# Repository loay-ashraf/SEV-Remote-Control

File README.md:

# SEV Remote Control
Smart Electric Vehicle remote control implemented using AVR 8-bit microcontroller and Android companion app as a part of EV car conversion graduation project for Mechatronics Engineering Bachelor - Fall 2018.

## Overview
This section gives an overview of the system.

### Concept

SEV remote control is done via means of bluetooth communication between AVR controller board and any bluetooth-enabled device (Android smartphone for example).

### System Layout
System is divided into two separate modules that communicate with each other to acheive the desired output, which are:

#### SEV Controller Board Module

Controller board controls a set of relays and DAC units each connected to a specific actuator in the car.

#### SEV Companion App Module

Companion app sends commands via bluetooth to control each actuator.

## Discussion
This section discusses desicions made regarding design and implementation.

### Microcontroller

We opted for ATmega32 for SEV controller board as it has USART module and enough pins to control relays and DACs.

### Communication Protocol

We used USART protocol in order to communicate with the HC-05 bluetooth module.

### Android IDE

We used free MIT App Inventor as we lacked experience in Android app development while App Inventor offered shallow learning curve and a ton of tutorials available.

## Screenshots

[Screenshots of the companion app](Software/Companion%20App/Screenshots)

## Built With
- Atmel Studio 7 - The official AVR IDE
- AVR-gcc V5.4 - C compiler
- GNU Make - auto-generated makefile
- MIT App Inventor - Android IDE
- CadSoft EAGLE - PCB design tool

## Authors
Loay Ashraf - <loay.ashraf.96@gmail.com>

Mohamed Gamal - <muhammed.gamal051@gmail.com>

## License
This project is licensed under the MIT License - see the LICENSE.md file for details

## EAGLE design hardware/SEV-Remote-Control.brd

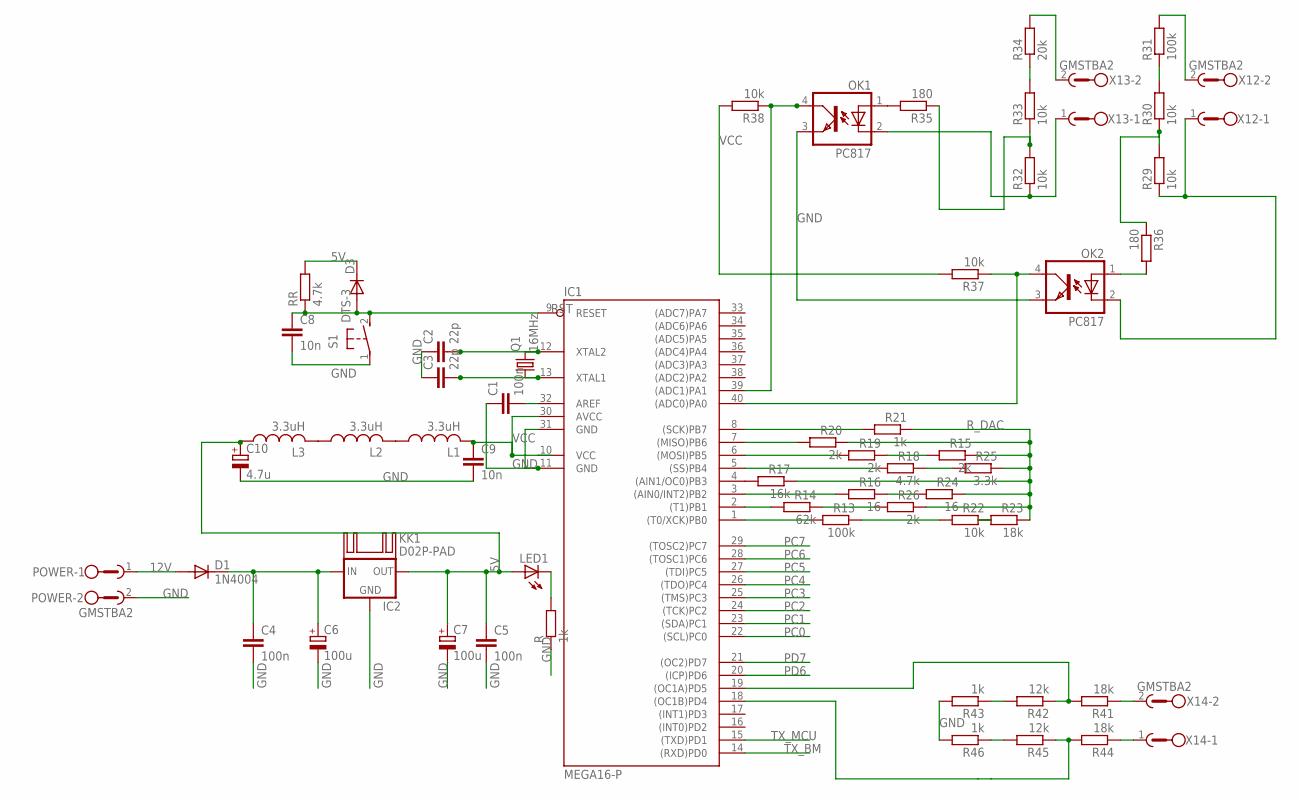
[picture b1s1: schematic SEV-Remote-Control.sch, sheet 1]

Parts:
C1, C4, C5: 100n; C025-025X050
C2, C3: 22p; C025-025X050
C6, C7: 100u; E2,5-6
C8, C9: 10n; C025-025X050
C10: 4.7u; E2,5-6
D1: 1N4004; DO41-10
D3: 1N4148DO35-10; DO35-10
IC1: MEGA16-P; DIL40
IC2: 78XXS
KK1: D02P-PAD; D02PA-PAD
L1, L2, L3: 3.3uH; 0207/7
LED1: LED5MM
OK1, OK2: PC817; DIL04
POWER: GMSTBA2
Q1: 16MHz; HC49/S
R, R21, R43, R46: 1k; 0207/10
R13, R31: 100k; 0207/10
R14: 62k; 0207/10
R15, R19, R20, R26: 2k; 0207/10
R16, R24: 16; 0207/10
R17: 16k; 0207/10
R18: 4.7k; 0207/10
R22, R29, R30, R32, R33, R37, R38: 10k; 0207/10
R23, R41, R44: 18k; 0207/10
R25: 3.3k; 0207/10
R34: 20k; 0207/10
R35, R36: 180; 0207/10
R42, R45: 12k; 0207/10
RR: 4.7k; 0207/10
S1: DTS-3
X12, X13, X14: GMSTBA2

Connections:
5V: C5.1, C7.+, C10.+, D3.C, IC2.OUT, L3.1, LED1.A, RR.2
12V: D1.A, POWER.1; also elsewhere on the board
GND: C1.1, C2.1, C3.1, C4.2, C5.2, C6.-, C7.-, C8.2, C9.2, C10.-, IC1.11 (GND), IC1.31 (GND), IC2.GND, OK1.3 (EMIT), OK2.3 (EMIT), POWER.2, R.1, R43.2, R46.2, S1.1; also elsewhere on the board
IN: C4.1, C6.+, D1.C, IC2.IN
unnamed: R15.2, R19.1
unnamed: R13.1, R22.2
unnamed: LED1.K (C), R.2
unnamed: C2.2, IC1.12 (XTAL2), Q1.2
unnamed: R22.1, R23.2
unnamed: C1.2, IC1.32 (AREF)
unnamed: R16.1, R24.2
unnamed: C3.2, IC1.13 (XTAL1), Q1.1
unnamed: R18.1, R25.2
unnamed: R14.1, R26.2
unnamed: L1.1, L2.2
unnamed: L2.1, L3.2
unnamed: R29.2, R30.1, R36.1
unnamed: R30.2, R31.1
unnamed: R31.2, X12.2
unnamed: IC1.40 ((ADC0)PA0), OK2.4 (COL), R37.1
unnamed: OK1.1 (A), R35.2
unnamed: R33.2, R34.1
unnamed: R34.2, X13.2
unnamed: OK1.2 (C), R32.1, X13.1
unnamed: R32.2, R33.1, R35.1
unnamed: OK2.1 (A), R36.2
unnamed: IC1.2 ((T1)PB1), R14.2
unnamed: OK2.2 (C), R29.1, X12.1
unnamed: IC1.39 ((ADC1)PA1), OK1.4 (COL), R38.1
unnamed: R44.1, X14.1
unnamed: IC1.1 ((T0/XCK)PB0), R13.2
unnamed: IC1.3 ((AIN0/INT2)PB2), R16.2
unnamed: IC1.4 ((AIN1/OC0)PB3), R17.2
unnamed: IC1.5 ((SS)PB4), R18.2
unnamed: IC1.6 ((MOSI)PB5), R19.2
unnamed: IC1.7 ((MISO)PB6), R20.2
unnamed: IC1.8 ((SCK)PB7), R21.2
unnamed: R41.1, X14.2
unnamed: IC1.19 ((OC1A)PD5), R41.2, R42.1
unnamed: IC1.18 ((OC1B)PD4), R44.2, R45.1
unnamed: R42.2, R43.1
unnamed: R45.2, R46.1
PC0: IC1.22 ((SCL)PC0); also elsewhere on the board
PC1: IC1.23 ((SDA)PC1); also elsewhere on the board
PC2: IC1.24 ((TCK)PC2); also elsewhere on the board
PC3: IC1.25 ((TMS)PC3); also elsewhere on the board
PC4: IC1.26 ((TDO)PC4); also elsewhere on the board
PC5: IC1.27 ((TDI)PC5); also elsewhere on the board
PC6: IC1.28 ((TOSC1)PC6); also elsewhere on the board
PC7: IC1.29 ((TOSC2)PC7); also elsewhere on the board
PD6: IC1.20 ((ICP)PD6); also elsewhere on the board
PD7: IC1.21 ((OC2)PD7); also elsewhere on the board
RST: C8.1, D3.A, IC1.9 (RESET), RR.1, S1.2
R_DAC: R15.1, R17.1, R20.1, R21.1, R23.1, R24.1, R25.1, R26.1; also elsewhere on the board
TX_BM: IC1.14 ((RXD)PD0); also elsewhere on the board
TX_MCU: IC1.15 ((TXD)PD1); also elsewhere on the board
VCC: C9.1, IC1.10 (VCC), IC1.30 (AVCC), L1.2, R37.2, R38.2; also elsewhere on the board

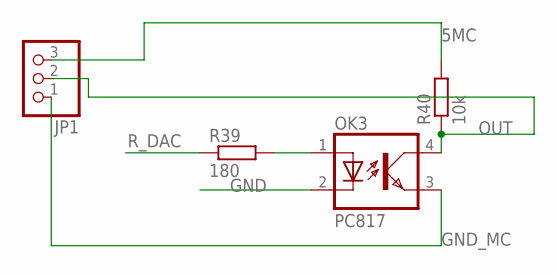
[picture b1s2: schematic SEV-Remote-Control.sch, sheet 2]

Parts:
JP1: PINHD-1X3; 1X03
OK3: PC817; DIL04
R39: 180; 0207/10
R40: 10k; 0207/10

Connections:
5MC: JP1.3, R40.2
GND: OK3.2 (C); also elsewhere on the board
GND_MC: JP1.1, OK3.3 (EMIT)
unnamed: OK3.1 (A), R39.2
OUT: JP1.2, OK3.4 (COL), R40.1
R_DAC: R39.1; also elsewhere on the board

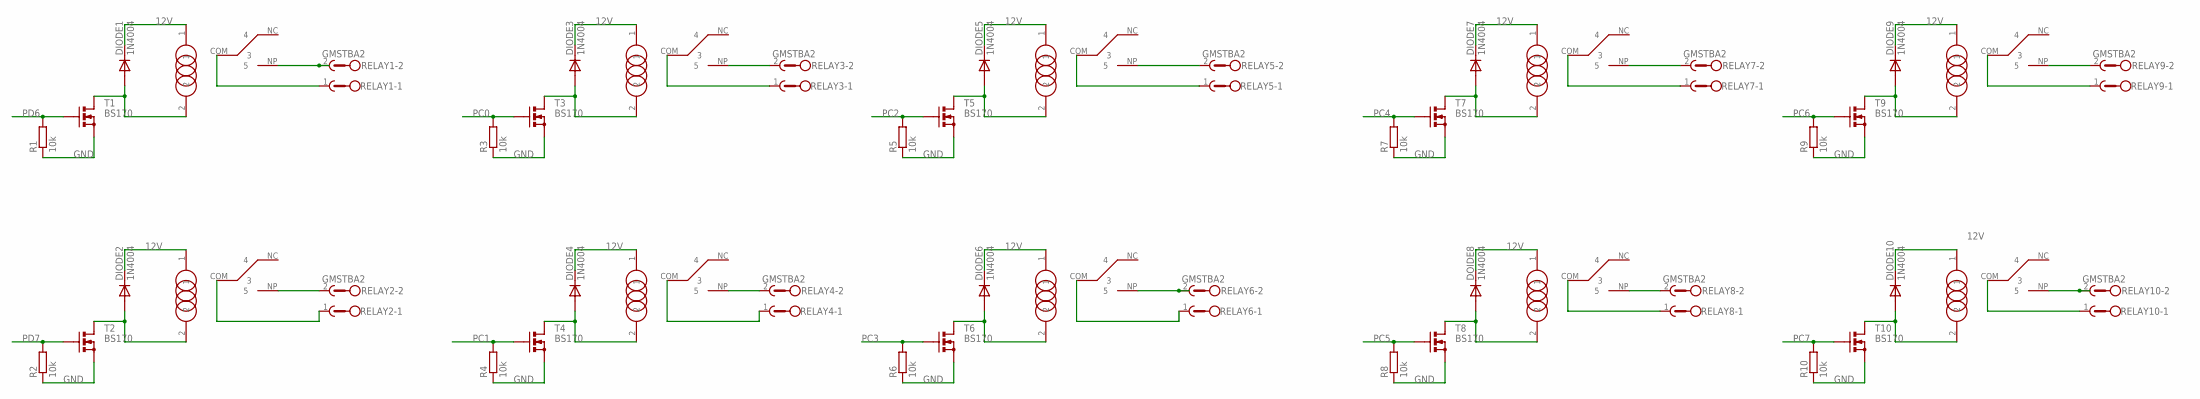
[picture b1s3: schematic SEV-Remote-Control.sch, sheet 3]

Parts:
DIODE1, DIODE2, DIODE3, DIODE4, DIODE5, DIODE6, DIODE7, DIODE9, DIODE10: 1N4004; DO41-10
DOIDE8: 1N4004; DO41-10
R1, R2, R3, R4, R5, R6, R7, R8, R9, R10: 10k; 0207/10
REL3: RELAY
RELAY1, RELAY2, RELAY3, RELAY4, RELAY5, RELAY6, RELAY7, RELAY8, RELAY9, RELAY10: GMSTBA2
T1, T2, T3, T4, T5, T6, T7, T8, T9, T10: BS170; SOT54E
U$1, U$2, U$3, U$5, U$6, U$7, U$8, U$9, U$10: RELAY

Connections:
12V: DIODE1.C, DIODE2.C, DIODE3.C, DIODE4.C, DIODE5.C, DIODE6.C, DIODE7.C, DIODE9.C, DIODE10.C, DOIDE8.C, REL3.1, U$1.1, U$2.1, U$3.1, U$5.1, U$6.1, U$7.1, U$8.1, U$9.1, U$10.1; also elsewhere on the board
COM: RELAY10.1, U$3.COM (3)
COM1: RELAY2.1, U$9.COM (3)
GND: R1.1, R2.1, R3.1, R4.1, R5.1, R6.1, R7.1, R8.1, R9.1, R10.1, T1.S, T2.S, T3.S, T4.S, T5.S, T6.S, T7.S, T8.S, T9.S, T10.S; also elsewhere on the board
unnamed: REL3.COM (3), RELAY3.1
unnamed: DIODE3.A, REL3.2, T3.D
unnamed: RELAY8.1, U$1.COM (3)
unnamed: DOIDE8.A, T8.D, U$1.2
unnamed: DIODE9.A, T9.D, U$2.2
unnamed: RELAY9.2, U$2.NP (5)
unnamed: RELAY6.2, U$8.NP (5)
unnamed: DIODE10.A, T10.D, U$3.2
unnamed: DIODE6.A, T6.D, U$8.2
unnamed: DIODE2.A, T2.D, U$9.2
unnamed: RELAY7.2, U$10.NP (5)
unnamed: REL3.NP (5), RELAY3.2
unnamed: DIODE7.A, T7.D, U$10.2
unnamed: RELAY4.1, U$5.COM (3)
unnamed: DIODE4.A, T4.D, U$5.2
unnamed: RELAY9.1, U$2.COM (3)
unnamed: RELAY5.1, U$6.COM (3)
unnamed: RELAY8.2, U$1.NP (5)
unnamed: RELAY4.2, U$5.NP (5)
unnamed: RELAY6.1, U$8.COM (3)
unnamed: RELAY1.1, U$7.COM (3)
unnamed: RELAY7.1, U$10.COM (3)
unnamed: DIODE5.A, T5.D, U$6.2
unnamed: RELAY5.2, U$6.NP (5)
unnamed: DIODE1.A, T1.D, U$7.2
unnamed: RELAY1.2, U$7.NP (5)
NP1: RELAY2.2, U$9.NP (5)
PC0: R3.2, T3.G; also elsewhere on the board
PC1: R4.2, T4.G; also elsewhere on the board
PC2: R5.2, T5.G; also elsewhere on the board
PC3: R6.2, T6.G; also elsewhere on the board
PC4: R7.2, T7.G; also elsewhere on the board
PC5: R8.2, T8.G; also elsewhere on the board
PC6: R9.2, T9.G; also elsewhere on the board
PC7: R10.2, T10.G; also elsewhere on the board
PD6: R1.2, T1.G; also elsewhere on the board
PD7: R2.2, T2.G; also elsewhere on the board
RELAY6: RELAY10.2, U$3.NP (5)

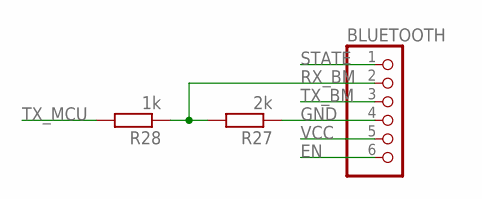
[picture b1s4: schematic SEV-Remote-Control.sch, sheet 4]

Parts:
BLUETOOTH: PINHD-1X6; 1X06
R27: 2k; 0207/10
R28: 1k; 0207/10

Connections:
EN: BLUETOOTH.6
GND: BLUETOOTH.4, R27.1; also elsewhere on the board
RX_BM: BLUETOOTH.2, R27.2, R28.1
STATE: BLUETOOTH.1
TX_BM: BLUETOOTH.3; also elsewhere on the board
TX_MCU: R28.2; also elsewhere on the board
VCC: BLUETOOTH.5; also elsewhere on the board

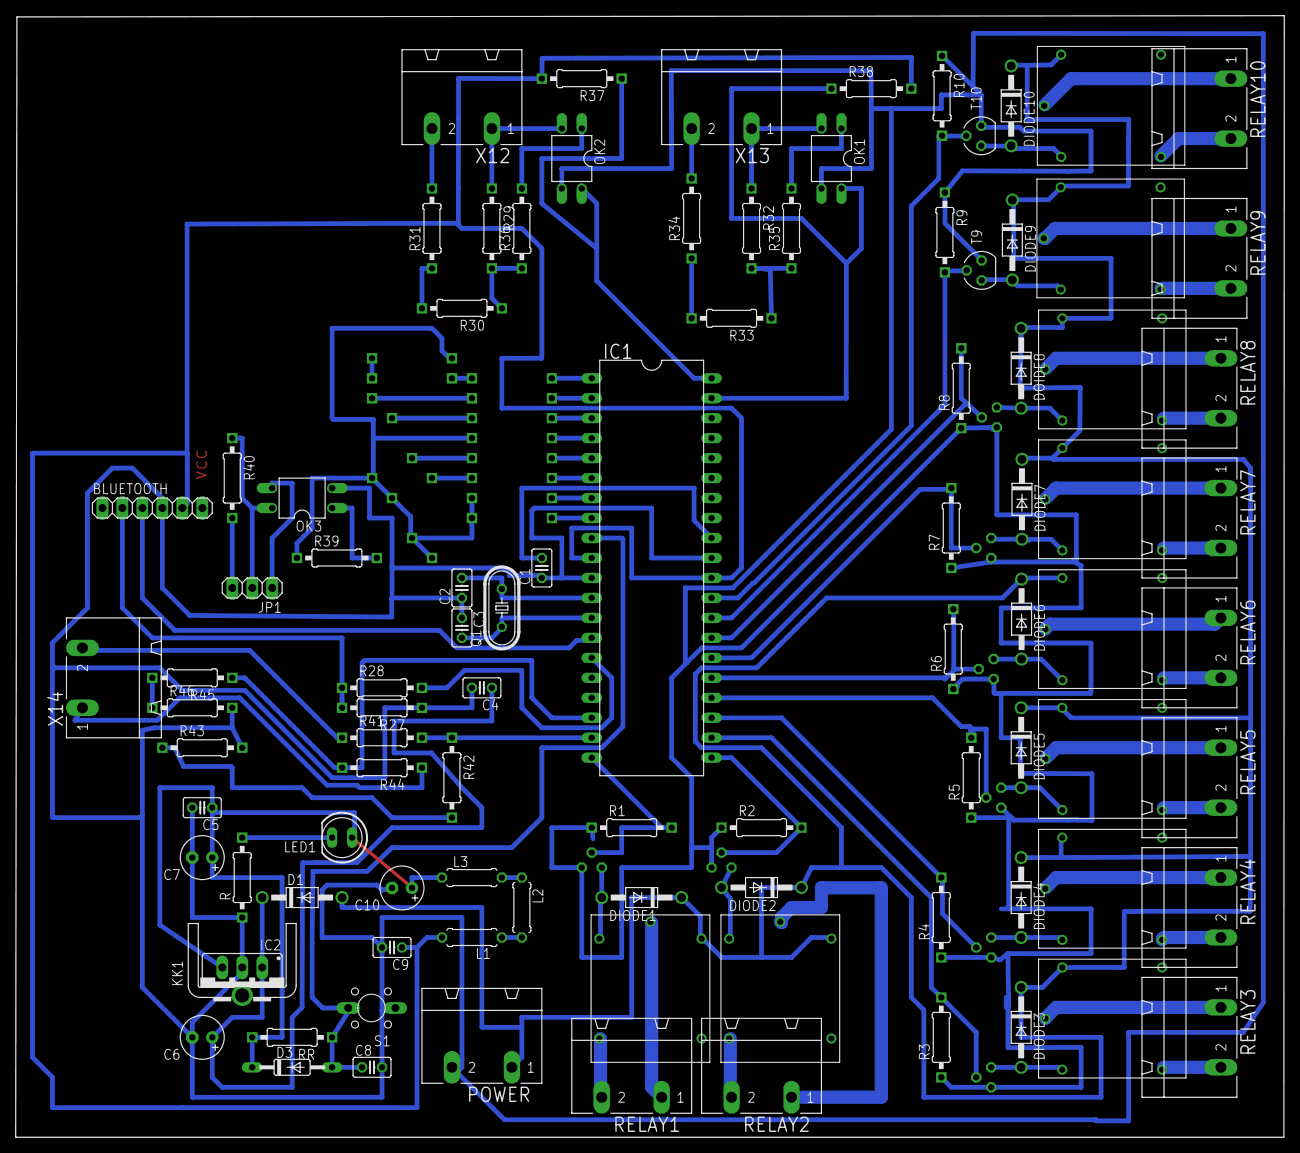
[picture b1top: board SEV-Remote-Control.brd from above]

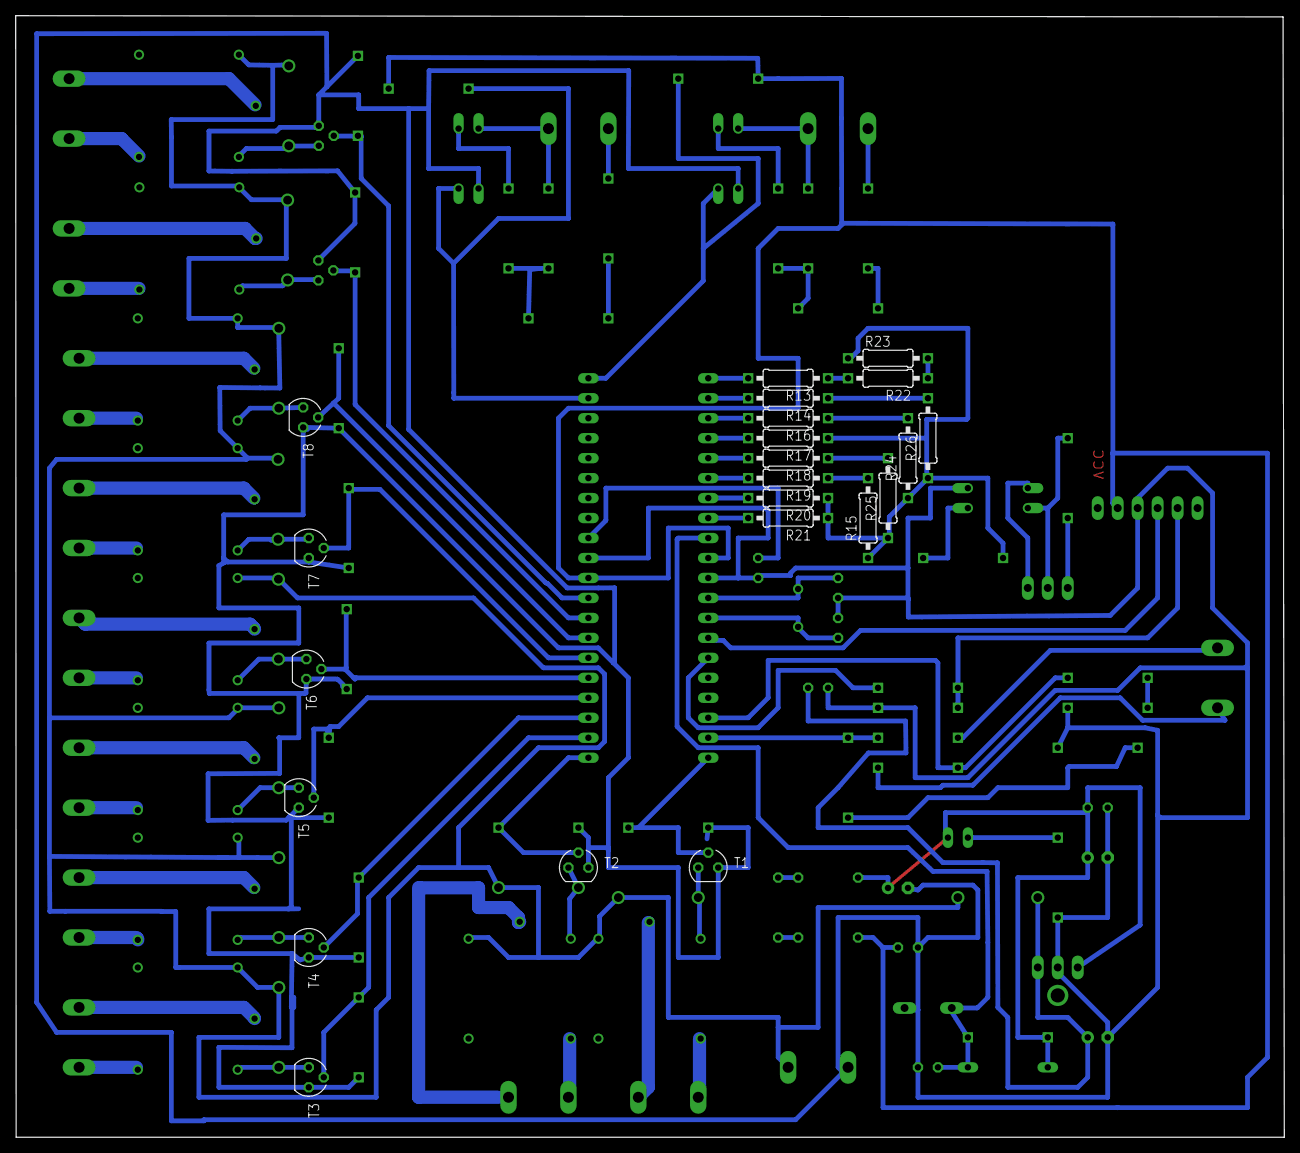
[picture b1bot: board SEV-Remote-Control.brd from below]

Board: 2 copper layers, 161.3 x 142.6 mm, 116 parts (22 on the bottom side), 92 nets.

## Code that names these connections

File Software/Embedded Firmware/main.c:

/** @mainpage About
 *  @author Loay Ashraf <loay.ashraf.96@gmail.com>
 *  @version 1.0.0
 *
 *  This program is implemented on ATmega16/32 running at 16 MHZ
 *	CPU clock, it basically receives commands from Android companion
 *	application via Bluetooth using the widely common HC-05 Bluetooth 
 *	Module, it acts upon the command received by -for example- turning 
 *	ON a relay which activates certain feature of the vehicle; means of
 *	feedback include battery voltage and speed of the motor. 
 *  
 *	@pinassignments
 *
 *	- PB0-7: DAC output signal
 *	- PC0-7, PD6-7: Relay output signal
 *	- PD0: USART RX signal
 *	- PD1: USART TX signal
 *
 *	@see main.c
 */

/** @file main.c
 *  @brief includes the main function
 *  
 *	the main function periodically checks for incoming commands
 *	via USART interface, if one is received it starts processing 
 *	the command and takes the action that corresponds to the 
 *	command received. 
 *
 *  @author Loay Ashraf
 *	@version 1.0.0
 *  @pre include USART.h, string.h and set F_CPU in micro_config.h
 *  @bug no known bugs
 *  @see micro_config.h
 */

//------------INCLUDE DEVICE DRIVERS------------//

#include "ADC.h"
#include "USART.h"

//------------DECLARE GLOBAL VARIABLES------------//
/** @var char* received_ptr
 *  @brief Stores memory address of received command
 */

/** @var char* received_str
 *  @brief Stores data of received command
 */

/** @var char* res_str
 *  @brief Stores result of float conversion
 */

/** @var char* ON_flag
 *  @brief Stores ON status of the all features (0 for OFF, 1 for ON)
 */

/** @var float Volt
 *  @brief Current battery voltage value
 */

/** @var float Speed
 *  @brief Current motor speed value
 */

/** @var uint8 i
 *  @brief Counter that iterates through received command
 */

/** @var uint8 thumb_position
 *  @brief Stores current slider position in the android app
 */

char * received_ptr;
char received_str[10], res_str[7], ON_flag[7];
float Volt, Speed; 
uint8 i, thumb_position;

/** @brief the main function
 *
 *  see main.c description
 *
 *  @return exit status (1 or 0)
 */
int main(void){
	
	//------------INITIALIZE I/O PORTS------------//
	
	DDRB = 0xFF;
	DDRC = 0xFF;
	DDRD = 0xC0;
	
	//------------INITIALIZE ADC INTERFACE------------//
	
	ADC_Init(AVCC, RIGHT_ADJ, 128);	// AVCC as Vref, right adjusted result (10-bit), 128 prescaler
	ADC_Read(ADC0);
	ADC_Read(ADC1);
	
	//------------INITIALIZE USART INTERFACE------------//
	
	USART_init(AS, NORMAL_SPEED, 8, NO_PARITY, 1);	// asynchronous, 8-bit data frame, no parity check, one stop bit
	USART_set_baudrate(38400);						// 38400 bits/sec baud rate
	USART_enable();									// enable USART interface

	while (1){
		
		//------------RECIEVE NEW COMMAND AND PROCESS IT INTO A STRING------------//
		
		received_ptr = USART_Receive_str();		// receive new command
		for(i=0;i<10;i++)
		received_str[i]=*received_ptr++;		// store received command data in array
		
		//------------CHECK RECEIVED COMMAND AND TAKE CORRESPONDING ACTION------------//
		
		if(!strcmp(received_str,"Voltage")){
			
			Volt = ((ADC_Read(ADC0)/1023.0)*60);
			dtostrf(Volt, 6, 2,res_str);
			USART_Transmit_str(res_str);

		}else if (!strcmp(received_str,"RPM")){
			
			Speed = ((ADC_Read(ADC1)/1023.0)*4900);
			dtostrf(Speed, 6, 2,res_str);
			USART_Transmit_str(res_str);
			
		}else if (!strcmp(received_str,"one")){
			
			// forward action
			PORTC |= 0x01;

		}else if (!strcmp(received_str,"two")){
			
			// reverse action
			PORTC |= 0x02;
			_delay_ms(1);
			PORTC |= 0x01;
	
		}else if (!strcmp(received_str,"three")){
			
			// brake action
			PORTC |= 0x04;
			_delay_ms(1);
			PORTC &= ~0x03;
			_delay_ms(10);
			PORTC &= ~0x04;

		}else if (!strcmp(received_str,"four")){
			
			// low headlights
			if(!ON_flag[0]){
			PORTC |= 0x08;
			ON_flag[0] = 1;
			}else{
			PORTC &= ~0x08;	
			ON_flag[0] = 0;	
			}

		}else if (!strcmp(received_str,"five")){
			
			// high headlights
			if(!ON_flag[1]){
			PORTC |= 0x10;
			ON_flag[1] = 1;
			}else{
			PORTC &= ~0x10;
			ON_flag[1] = 0;
			}

		}else if (!strcmp(received_str,"six")){
			
			// right signs
			if(!ON_flag[2]){
			PORTC |= 0x20;
			ON_flag[2] = 1;
			}else{
			PORTC &= ~0x20;
			ON_flag[2] = 0;
			}

		}else if (!strcmp(received_str,"seven")){
			
			// left signs
			if(!ON_flag[3]){
			PORTC |= 0x40;
			ON_flag[3] = 1;
			}else{
			PORTC &= ~0x40;
			ON_flag[3] = 0;
			}

		}else if (!strcmp(received_str,"eight")){
			
			// waiting signs
			if(!ON_flag[4]){
			PORTC |= 0x80;
			ON_flag[4] = 1;
			}else{
			PORTC &= ~0x80;
			ON_flag[4] = 0;
			}

		}else if (!strcmp(received_str,"nine")){
			
			// lower car roof
			if(!ON_flag[5]){
			PORTD |= 0x40;
			ON_flag[5] = 1;
			}else{
			PORTD &= ~0x40;
			ON_flag[5] = 0;
			}

		}else if (!strcmp(received_str,"ten")){
			
			// raise car roof
			if(!ON_flag[6]){
			PORTD |= 0x80;
			ON_flag[6] = 1;
			}else{
			PORTD &= ~0x80;
			ON_flag[6] = 0;
			}

		}else{
			
			// receive slider position in the app and set speed
			thumb_position = atoi(received_str);
			PORTB = (255-thumb_position);
			
		}}
	}

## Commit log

2021-03-25 Add software source files
